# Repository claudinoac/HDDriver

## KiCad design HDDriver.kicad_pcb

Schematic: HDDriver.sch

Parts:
C1: 100u; C_Radial_D8_L11.5_P3.5
C2: 10u; C_Radial_D5_L11_P2.5
CON1: +12VDC; BARREL_JACK
D1, D2, D3: D; D_DO-41_SOD81_P7.62mm_Horizontal
P1: UPLOAD; Pin_Header_Straight_1x05_Pitch2.54mm
P2: MOTOR CONNECT; Pin_Header_Straight_1x04_Pitch2.54mm
Q1, Q2, Q3: TIP122; TO-220_Vertical
R1, R2, R3: 2K7; RC03
U1: ATTINY85-20PU; DIP-8_W7.62mm_LongPads
U2: L7805; TO-220_Vertical

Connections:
+5V: C2.1, U1.8 (VCC), U2.3
COMMON: C1.1, CON1.1, D1.1, D2.1, D3.1, P2.4, U2.1
GND: C1.2, C2.2, CON1.2, CON1.3, P1.1, Q1.3 (E), Q2.3 (E), Q3.3 (E), U1.4 (GND), U2.2
unnamed: Q1.1 (B), R1.1
unnamed: Q2.1 (B), R2.1
unnamed: Q3.1 (B), R3.1
R: D1.2, P2.1, Q1.2 (C)
R_CTRL: P1.4, R1.2, U1.5 (PB0(MOSI/DI/SDA/AIN0/OC0A/OC1A/AREF/PCI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)
S: D2.2, P2.2, Q2.2 (C)
S_CTRL: P1.3, R2.2, U1.6 (PB1(MISO/DO/AIN1/OC0B/OC1A/PCINT1))
T: D3.2, P2.3, Q3.2 (C)
T_CTRL: P1.2, R3.2, U1.7 (PB2(SCK/USCK/SCL/T0/INT0/ADC1/PCINT2))
~RESET: P1.5, U1.1 (PB5(~RESET~/dW/ADC0/PCINT5))

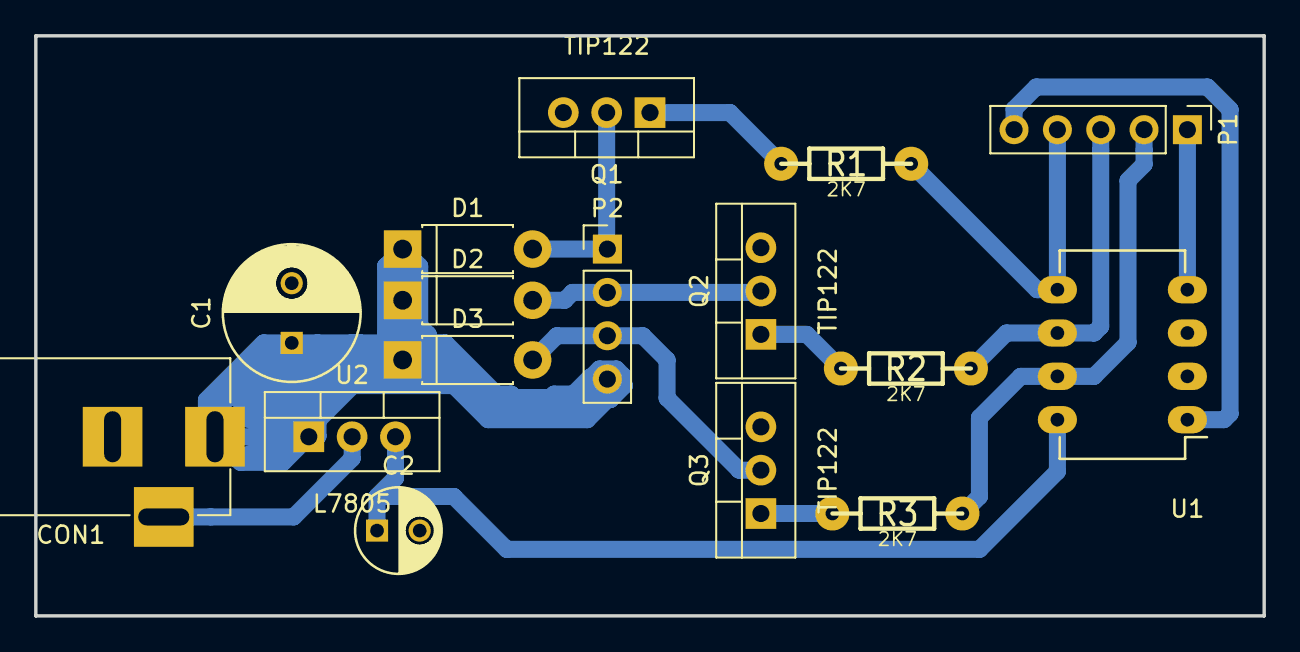
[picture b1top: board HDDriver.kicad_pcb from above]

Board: 2 copper layers, 72.0 x 34.0 mm, 16 parts (0 on the bottom side), 13 nets.

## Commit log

2018-06-12 ADD: All PCB fabrication files
